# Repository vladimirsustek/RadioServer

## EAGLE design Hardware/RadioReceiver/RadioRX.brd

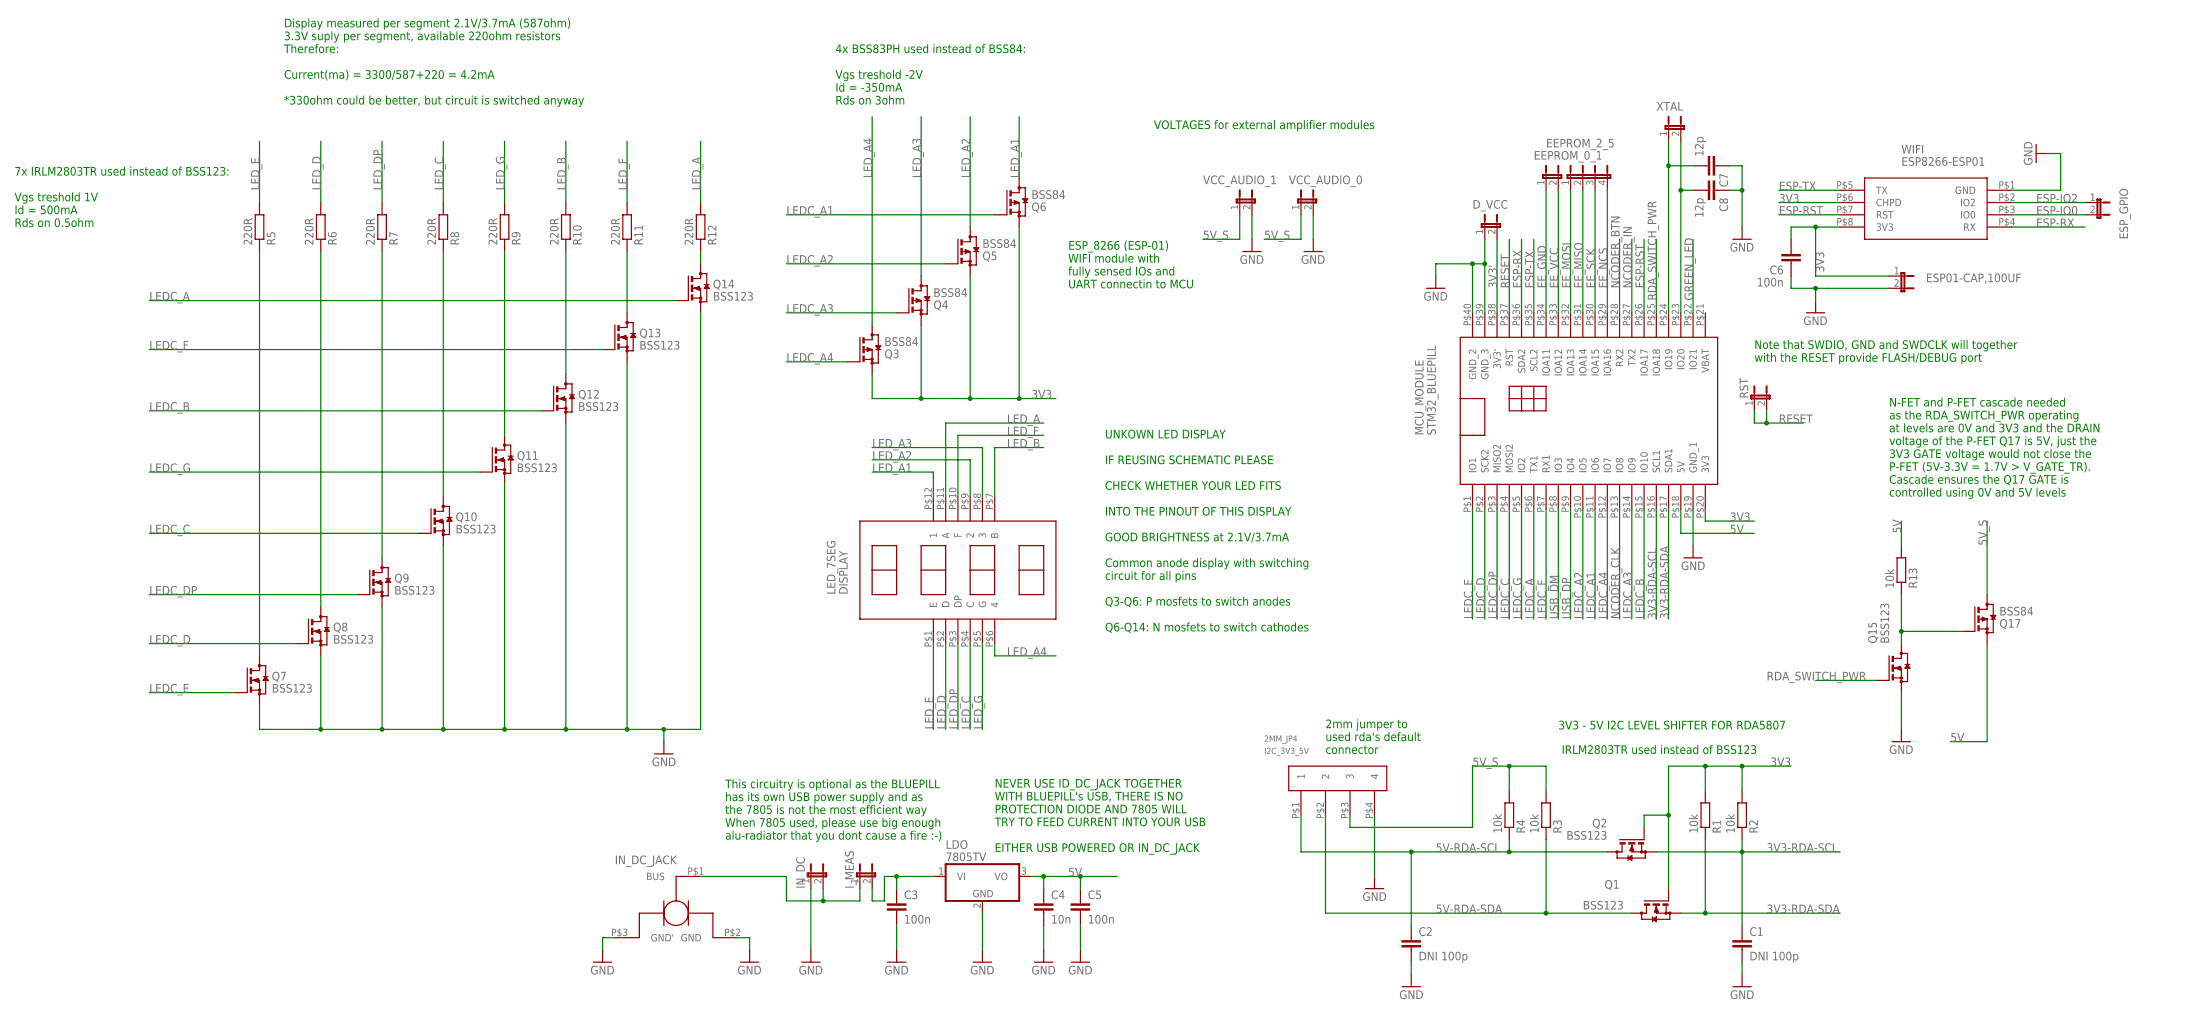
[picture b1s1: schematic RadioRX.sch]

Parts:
C1, C2: DNI 100p; C0805
C3, C5, C6: 100n; C0805
C4: 10n; C0805
C7, C8: 12p; C0603
DISPLAY: LED_7SEG
D_VCC: JP1E; JP1
EEPROM_0_1: JP1E; JP1
EEPROM_2_5: JP4E; JP4
ESP01-CAP,100UF: JP1E; JP1
ESP_GPIO: JP1E; JP1
I2C_3V3_5V: 2MM_JP4
IN_DC: JP1E; JP1
IN_DC_JACK: DC_CONN
I_MEAS: JP1E; JP1
LDO: 7805TV; TO220V
MCU_MODULE: STM32_BLUEPILL
Q1, Q2, Q7, Q8, Q9, Q10, Q11, Q12, Q13, Q14, Q15: BSS123; SOT23
Q3, Q4, Q5, Q6, Q17: BSS84; SOT23
R1, R2, R3, R4, R13: 10k; R0805
R5, R6, R7, R8, R9, R10, R11, R12: 220R; R0805
RST: JP1E; JP1
VCC_AUDIO_0, VCC_AUDIO_1: JP1E; JP1
WIFI: ESP8266-ESP01
XTAL: JP1E; JP1

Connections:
3V3: C6.2, ESP01-CAP,100UF.1, MCU_MODULE.P$20 (3V3), Q1.1 (G), Q2.1 (G), Q3.2 (S), Q4.2 (S), Q5.2 (S), Q6.2 (S), R1.2, R2.2, WIFI.P$6 (CHPD), WIFI.P$8 (3V3)
3V3': D_VCC.2, MCU_MODULE.P$38 (3V3')
3V3-RDA-SCL: C1.1, MCU_MODULE.P$16 (SCL1), Q2.2 (S), R2.1
3V3-RDA-SDA: MCU_MODULE.P$17 (SDA1), Q1.2 (S), R1.1
5V: C4.1, C5.1, LDO.3 (VO), MCU_MODULE.P$18 (5V), Q17.2 (S), R13.2
5V-RDA-SCL: C2.1, I2C_3V3_5V.P$1 (1), Q2.3 (D), R4.1
5V-RDA-SDA: I2C_3V3_5V.P$2 (2), Q1.3 (D), R3.1
5V_S: I2C_3V3_5V.P$3 (3), Q17.3 (D), R3.2, R4.2, VCC_AUDIO_0.1, VCC_AUDIO_1.1
EE_GND: EEPROM_0_1.1, MCU_MODULE.P$34 (IOA11)
EE_MISO: EEPROM_2_5.2, MCU_MODULE.P$31 (IOA14)
EE_MOSI: EEPROM_2_5.1, MCU_MODULE.P$32 (IOA13)
EE_NCS: EEPROM_2_5.4, MCU_MODULE.P$29 (IOA16)
EE_SCK: EEPROM_2_5.3, MCU_MODULE.P$30 (IOA15)
EE_VCC: EEPROM_0_1.2, MCU_MODULE.P$33 (IOA12)
ESP-IO0: ESP_GPIO.2, WIFI.P$3 (IO0)
ESP-IO2: ESP_GPIO.1, WIFI.P$2 (IO2)
ESP-RST: MCU_MODULE.P$26 (IOA17), WIFI.P$7 (RST)
ESP-RX: MCU_MODULE.P$36 (SDA2), WIFI.P$4 (RX)
ESP-TX: MCU_MODULE.P$35 (SCL2), WIFI.P$5 (TX)
GND: C1.2, C2.2, C3.2, C4.2, C5.2, C6.1, C7.1, C8.1, D_VCC.1, ESP01-CAP,100UF.2, I2C_3V3_5V.P$4 (4), IN_DC.1, IN_DC_JACK.P$2 (GND), IN_DC_JACK.P$3 (GND'), LDO.2 (GND), MCU_MODULE.P$19 (GND_1), MCU_MODULE.P$39 (GND_3), MCU_MODULE.P$40 (GND_2), Q7.2 (S), Q8.2 (S), Q9.2 (S), Q10.2 (S), Q11.2 (S), Q12.2 (S), Q13.2 (S), Q14.2 (S), Q15.2 (S), VCC_AUDIO_0.2, VCC_AUDIO_1.2, WIFI.P$1 (GND)
GREEN_LED: MCU_MODULE.P$22 (IO21)
LEDC_A: MCU_MODULE.P$6 (TX1), Q14.1 (G)
LEDC_A1: MCU_MODULE.P$11 (IO6), Q6.1 (G)
LEDC_A2: MCU_MODULE.P$10 (IO5), Q5.1 (G)
LEDC_A3: MCU_MODULE.P$14 (IO9), Q4.1 (G)
LEDC_A4: MCU_MODULE.P$12 (IO7), Q3.1 (G)
LEDC_B: MCU_MODULE.P$15 (IO10), Q12.1 (G)
LEDC_C: MCU_MODULE.P$4 (MOSI2), Q10.1 (G)
LEDC_D: MCU_MODULE.P$2 (SCK2), Q8.1 (G)
LEDC_DP: MCU_MODULE.P$3 (MISO2), Q9.1 (G)
LEDC_E: MCU_MODULE.P$1 (IO1), Q7.1 (G)
LEDC_F: MCU_MODULE.P$7 (RX1), Q13.1 (G)
LEDC_G: MCU_MODULE.P$5 (IO2), Q11.1 (G)
LED_A: DISPLAY.P$11 (A), R12.2
LED_A1: DISPLAY.P$12 (1), Q6.3 (D)
LED_A2: DISPLAY.P$9 (2), Q5.3 (D)
LED_A3: DISPLAY.P$8 (3), Q4.3 (D)
LED_A4: DISPLAY.P$6 (4), Q3.3 (D)
LED_B: DISPLAY.P$7 (B), R10.2
LED_C: DISPLAY.P$4 (C), R8.2
LED_D: DISPLAY.P$2 (D), R6.2
LED_DP: DISPLAY.P$3 (DP), R7.2
LED_E: DISPLAY.P$1 (E), R5.2
LED_F: DISPLAY.P$10 (F), R11.2
LED_G: DISPLAY.P$5 (G), R9.2
unnamed: C3.1, I_MEAS.2, LDO.1 (VI)
unnamed: IN_DC.2, IN_DC_JACK.P$1 (BUS), I_MEAS.1
unnamed: C8.2, MCU_MODULE.P$23 (IO20), XTAL.2
unnamed: C7.2, MCU_MODULE.P$24 (IO19), XTAL.1
unnamed: Q15.3 (D), Q17.1 (G), R13.1
unnamed: Q7.3 (D), R5.1
unnamed: Q8.3 (D), R6.1
unnamed: Q9.3 (D), R7.1
unnamed: Q10.3 (D), R8.1
unnamed: Q11.3 (D), R9.1
unnamed: Q12.3 (D), R10.1
unnamed: Q13.3 (D), R11.1
unnamed: Q14.3 (D), R12.1
NCODER_BTN: MCU_MODULE.P$28 (RX2)
NCODER_CLK: MCU_MODULE.P$13 (IO8)
NCODER_IN: MCU_MODULE.P$27 (TX2)
RDA_SWITCH_PWR: MCU_MODULE.P$25 (IOA18), Q15.1 (G)
RESET: MCU_MODULE.P$37 (RST), RST.1, RST.2
USB_DM: MCU_MODULE.P$8 (IO3)
USB_DP: MCU_MODULE.P$9 (IO4)

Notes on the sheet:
ESP_8266 (ESP-01) WIFI module with fully sensed IOs and UART connectin to MCU
VOLTAGES for external amplifier modules
3V3 - 5V I2C LEVEL SHIFTER FOR RDA5807
7x IRLM2803TR used instead of BSS123: Vgs treshold 1V Id = 500mA Rds on 0.5ohm
4x BSS83PH used instead of BSS84: Vgs treshold -2V Id = -350mA Rds on 3ohm
UNKOWN LED DISPLAY IF REUSING SCHEMATIC PLEASE CHECK WHETHER YOUR LED FITS INTO THE PINOUT OF THIS DISPLAY GOOD BRIGHTNESS at 2.1V/3.7mA Common anode display with switching circuit for all pins Q3-Q6: P mosfets to switch anodes Q6-Q14: N mosfets to switch cathodes
2mm jumper to used rda's default connector
IRLM2803TR used instead of BSS123
Display measured per segment 2.1V/3.7mA (587ohm) 3.3V suply per segment, available 220ohm resistors Therefore: Current(ma) = 3300/587+220 = 4.2mA *330ohm could be better, but circuit is switched anyway
Note that SWDIO, GND and SWDCLK will together with the RESET provide FLASH/DEBUG port
N-FET and P-FET cascade needed as the RDA_SWITCH_PWR operating at levels are 0V and 3V3 and the DRAIN voltage of the P-FET Q17 is 5V, just the 3V3 GATE voltage would not close the P-FET (5V-3.3V = 1.7V > V_GATE_TR). Cascade ensures the Q17 GATE is controlled using 0V and 5V levels
This circuitry is optional as the BLUEPILL has its own USB power supply and as the 7805 is not the most efficient way When 7805 used, please use big enough alu-radiator that you dont cause a fire :-)
NEVER USE ID_DC_JACK TOGETHER WITH BLUEPILL's USB, THERE IS NO PROTECTION DIODE AND 7805 WILL TRY TO FEED CURRENT INTO YOUR USB EITHER USB POWERED OR IN_DC_JACK

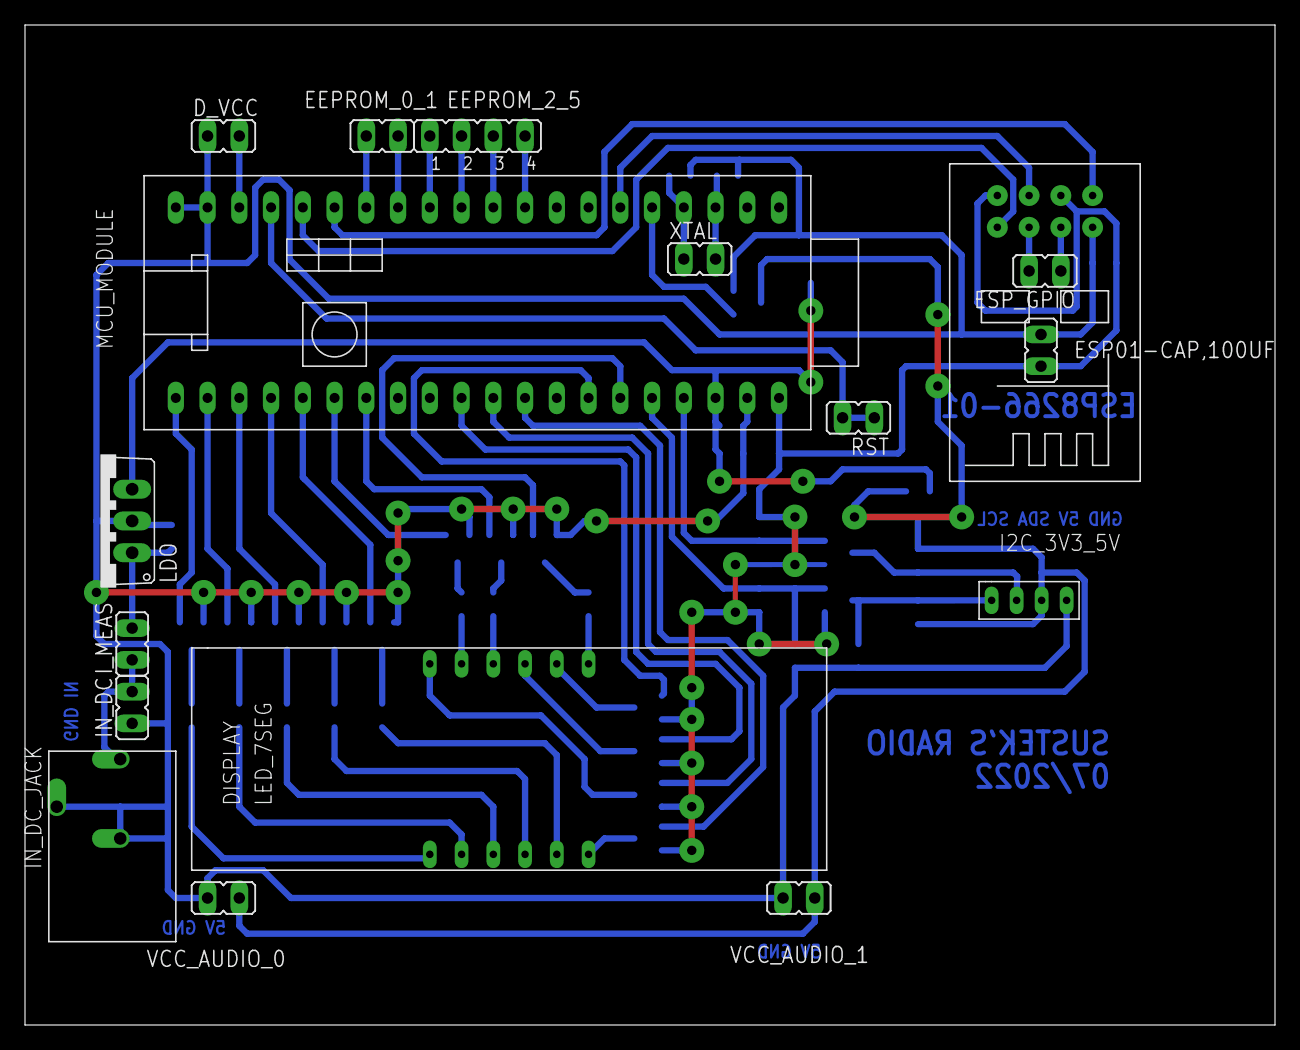
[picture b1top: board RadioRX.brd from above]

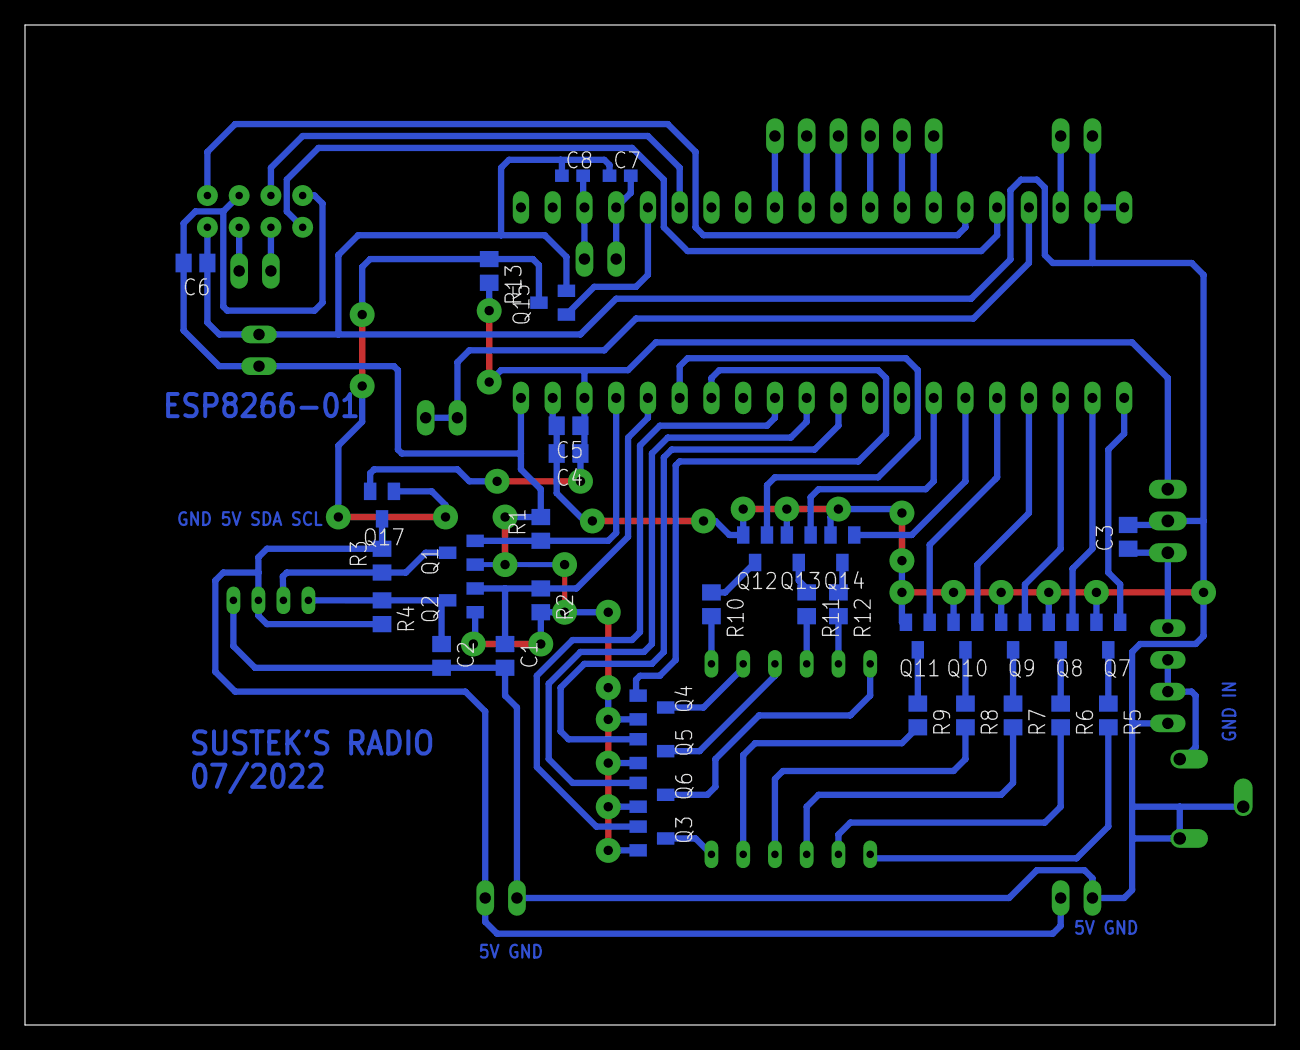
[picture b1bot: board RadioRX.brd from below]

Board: 2 copper layers, 100.0 x 80.0 mm, 54 parts (37 on the bottom side), 59 nets.

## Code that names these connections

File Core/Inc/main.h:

/* USER CODE BEGIN Header */
/**
  ******************************************************************************
  * @file           : main.h
  * @brief          : Header for main.c file.
  *                   This file contains the common defines of the application.
  ******************************************************************************
  * @attention
  *
  * Copyright (c) 2022 STMicroelectronics.
  * All rights reserved.
  *
  * This software is licensed under terms that can be found in the LICENSE file
  * in the root directory of this software component.
  * If no LICENSE file comes with this software, it is provided AS-IS.
  *
  ******************************************************************************
  */
/* USER CODE END Header */

/* Define to prevent recursive inclusion -------------------------------------*/
#ifndef __MAIN_H
#define __MAIN_H

#ifdef __cplusplus
extern "C" {
#endif

/* Includes ------------------------------------------------------------------*/
#include "stm32f1xx_hal.h"

/* Private includes ----------------------------------------------------------*/
/* USER CODE BEGIN Includes */

/* USER CODE END Includes */

/* Exported types ------------------------------------------------------------*/
/* USER CODE BEGIN ET */

/* USER CODE END ET */

/* Exported constants --------------------------------------------------------*/
/* USER CODE BEGIN EC */

/* USER CODE END EC */

/* Exported macro ------------------------------------------------------------*/
/* USER CODE BEGIN EM */

/* USER CODE END EM */

/* Exported functions prototypes ---------------------------------------------*/
void Error_Handler(void);

/* USER CODE BEGIN EFP */

/* USER CODE END EFP */

/* Private defines -----------------------------------------------------------*/
#define GREEN_LED_Pin GPIO_PIN_13
#define GREEN_LED_GPIO_Port GPIOC
#define RDA_SWITCH_PWR_Pin GPIO_PIN_0
#define RDA_SWITCH_PWR_GPIO_Port GPIOA
#define ESP_RST_Pin GPIO_PIN_1
#define ESP_RST_GPIO_Port GPIOA
#define NCODER_DT_Pin GPIO_PIN_3
#define NCODER_DT_GPIO_Port GPIOA
#define NCODER_BTN_Pin GPIO_PIN_2
#define NCODER_BTN_GPIO_Port GPIOA
#define SPI1_NCS_Pin GPIO_PIN_4
#define SPI1_NCS_GPIO_Port GPIOA
#define BMP_CS_Pin GPIO_PIN_0
#define BMP_CS_GPIO_Port GPIOB
#define LEDC_E_Pin GPIO_PIN_12
#define LEDC_E_GPIO_Port GPIOB
#define LEDC_D_Pin GPIO_PIN_13
#define LEDC_D_GPIO_Port GPIOB
#define LEDC_DP_Pin GPIO_PIN_14
#define LEDC_DP_GPIO_Port GPIOB
#define LEDC_C_Pin GPIO_PIN_15
#define LEDC_C_GPIO_Port GPIOB
#define LEDC_G_Pin GPIO_PIN_8
#define LEDC_G_GPIO_Port GPIOA
#define LEDC_A_Pin GPIO_PIN_9
#define LEDC_A_GPIO_Port GPIOA
#define LEDC_F_Pin GPIO_PIN_10
#define LEDC_F_GPIO_Port GPIOA
#define LEDC_A2_Pin GPIO_PIN_15
#define LEDC_A2_GPIO_Port GPIOA
#define LEDC_A1_Pin GPIO_PIN_3
#define LEDC_A1_GPIO_Port GPIOB
#define LEDC_A4_Pin GPIO_PIN_4
#define LEDC_A4_GPIO_Port GPIOB
#define NCODER_CLK_Pin GPIO_PIN_5
#define NCODER_CLK_GPIO_Port GPIOB
#define LEDC_B_Pin GPIO_PIN_6
#define LEDC_B_GPIO_Port GPIOB
#define LEDC_A3_Pin GPIO_PIN_7
#define LEDC_A3_GPIO_Port GPIOB
/* USER CODE BEGIN Private defines */

#define GPIO_ON_OFF(x) ((x) != 1 ? GPIO_PIN_SET : GPIO_PIN_RESET)

#define PLATFORM_DELAY_MS(MS)	(HAL_Delay(MS))
#define PLATFORM_TICK_MS(MS)	(HAL_GetTick(MS))

/* USER CODE END Private defines */

#ifdef __cplusplus
}
#endif

#endif /* __MAIN_H */

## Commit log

2022-07-16 Functiona stable 7-seg 4x digit LED display
2022-07-16 Fully functional VCOM cmd_dispatcher, output to LED
2022-08-11 Debugging DMA UART, working with parsing issues
2022-08-13 Finalized UART esp8266_port
2022-08-13 Added function waiting and checking response with timeout
2022-08-14 Functional HHTP BluePill's LEDON/LEDOFF, needs re-struct
2022-08-15 Commit before ESP restruct
2022-08-15 Restructualized (needs small hierarchy clean), functional radio
2022-08-16 Cleaned, functional HTTP controlled RDA5807M (basic functions)
2022-08-28 EEPROM Init, Write and Read works ..
2022-08-30 Fake change
2022-09-02 EEPROM_Modul almost OK write and read
2022-09-04 EEPROM 25AA1024 write, read 100% working
2022-09-04 All peripherals 100% supported by the cmd_dispatcher (RDA5807, ESP8266, 25AA1024)
2022-09-05 Restruct & HTTP init re-do (wifi connect)
2022-09-05 Ethernet controlled radio: freq and volume and value preserve
2022-09-06 Fully functional system, auto-solving HW faults (EEPROM, RADIO, WIFI)
2022-09-06 Added .launch .ioc and .ld files
2022-09-06 Minor changes, IP publish, webpage supporting CZ, AT, SK radios
2022-09-16 Cleaned HW, prepared for NCODER, time (slows 1minute/hours)
2022-09-20 Almost final state, just a 32.768 XTAL misses to be soldered
2022-09-20 Free pins set as an analog
2022-09-21 Functional RTC, improving Display app's FSM
2022-09-21 Moving out logic from main.c
2022-09-21 Functional Radio/Clock/Thermometer with 9-second FSM
2022-09-22 Release OK state 0, N-Coder misses
2022-09-24 Full system, needed RDA voltage turn on/off
2022-09-30 Corrected EEPROM flags
2022-09-30 By-Passed main:APP_UserInput due to being trigger when ESP_ProcessHTTP:Reset RDA Init and Rset modified
2022-10-15 Functional version without manual input
2022-10-16 Slightly changed definition of systemGlobalStates
2022-10-16 Functional N-Coder
2022-10-16 Functional NCODER release, APP functions divided into app and app_low
2023-05-20 Minor naming changes
